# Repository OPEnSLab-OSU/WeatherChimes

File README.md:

# WeatherChimes
## Completed By: Winnie Woo, Will Richards
---
### [WeatherChimes Wiki](https://github.com/OPEnSLab-OSU/OPEnS-Lab-Home/wiki/WeatherChimes)

WeatherChimes is an Internet of Things (IoT) project that uses Loom from the OPEnS lab to send weather data from an Arduino Feather M0 to [Max](https://cycling74.com/products/max). Much like how a wind chime converts wind information into sound, WeatherChimes strives to use a variety of weather sensors to gather data and then process that information into media like generative music and visual art for users. 

## Build Guide

[WeatherChimes Build Guide PDF](https://docs.google.com/document/d/1GEz6TniiCkyVJEQ1pW2CY4VUsa4j7f_cYcETQBzS96c/edit?usp=sharing)

## Before Installation
Before code can be uploaded to the Feather, download the [Arduino IDE software](https://www.arduino.cc/en/software) and set up the board profile to include the necessary libraries such as Loom, TSL2591, SHT30 and SDI-12, instructions for completing these steps are present in our [Quick Start Guide](https://github.com/OPEnSLab-OSU/Loom-V4). 

## Before Field Deployment
Please refer to the [WeatherChimes Operation Manual](https://docs.google.com/document/d/1b8-toOKHrU17z7gMsPlmyjn5y7iMVSKRvPj8aUgFDfA/edit?usp=sharing) for best practices in understanding and deploying WeatherChimes in the field.

## Setting Up Mosquitto
Mosquitto is an MQTT broker used for handling communication with remote devices over the MQTT protocol
* Download the [Mosquitto Broker](https://mosquitto.org/download/)
* In the directory of the mosquitto folder `C:\Program Files\mosquitto>`, create a mosquitto user/password: the command below will create a user with a name of your choosing, `mosquitto_passwd -c /etc/mosquitto/pwfile *name_of_choice*`.
You will be prompted to enter a password.
* Find the mosquitto.conf file and replace it with the [mosquitto.conf](https://github.com/OPEnSLab-OSU/WeatherChimes/blob/main/MongoDB/mosquitto.conf) file in this repo. For Windows, it can be located in `C:\Program Files\mosquitto\mosquitto.conf`
* In the newly replaced mosquitto.conf now replace line 34 with the path of the pwfile you just created.
* You are now set up to run the Mosquitto exectubale file to host the MQTT broker
<br>

## Setting Up MongoDB Database
[MongoDB Manual](https://docs.mongodb.com/manual/)\
A MongoDB instance should be running on the same server as the MQTT Broker

When data is recieved by the broker it will parse the topic out into the locations that data is stored in the database.

A basic MongoDB setup should suffice in most instances, remote access may be needed which can be completed [here](https://www.digitalocean.com/community/tutorials/how-to-configure-remote-access-for-mongodb-on-ubuntu-20-04)

It is **recommended** that you utilize [MongoDB Clusters](https://www.mongodb.com/basics/clusters) (specifically replica sets) for logging data as this will allow you to utilize the Max8 framework with less work.

<br>

## Connecting MQTT to MongodB using Node-RED

* Download [Node-RED](https://nodered.org/#get-started)
* Locate the `.node-red` folder on your machine. On Windows it can be located at `C:\Users\*your_username*\.node-red`
* Replace the contents of the `.node-red` folder with all the of files in the [Node-RED](https://github.com/OPEnSLab-OSU/WeatherChimes/tree/main/MongoDB/NodeRed) folder of this repository.
* TO run Node-RED, run the command `node-red` in the terminal
* Navigate to 127.0.0.1:1880. You can do this by running "http://localhost:1880/" on a browser. This allows you to interface with the Node-RED “flows”.

### Modifying the Node-RED flow
* The flow should intially look like this:

* The node farthest to the right is the Mongodb node. Click on that node and add your MongoDB cluster that you created earlier into the *Server* field

* Next, you need to specify what broker you want to connect to. Open the MQTT node (It looks like “+/+”). Click the pencil icon next to the Server field, this will allow us to add a new MQTT server. On the following page give it a name. Specify the server address and port (Figure 18) and then under security specify the username and password you use to authenticate with the broker.

<br>

## Loom Installation and MQTT Integration

Uploading the code to the Feather WiFi requires an USB cable. 
Download the code from the WeatherChimes Github repository and put WeatherChimes.ino, arduino_secrets.h and config.h in the same folder and open in Arduino.
Go to Tools >> Board >> Loom SAMD boards V4 >> Loomified Feather M0. Then also check Tools >> Ports and see if the correct port has been selected and the board is appearing on said port. Upload the code to the Feather, after it has finished compiling, check to see if the upload was successful by opening the Arduino IDE serial monitor to see successful connections to the WiFi and MQTT broker as well as the packets of data being sent over the MQTT protocol. 

The system clock needs to be set on the first run or when the Hypnos coin cell battery is reset. 
Within the weatherchimes.ino, line 141:

`80 hypnos.setInterruptDuration(TimeSpan(0, 0, 0, 10));`

The sampling interval could be changed to any duration. From left to right, the numbers represent days, hours, minutes and seconds. 

### Getting the Arduino to connect to the internet and send to Mosquitto

The arduino_secrets.h file also needs to include the MQTT settings. The BROKER_USER and BROKER_PASSWORD correspond to the username and password set on the MQTT broker. The SECRET_BROKER is the server (IP Address / Hostname) where the MQTT Broker is listening. The BROKER_PORT is where that MQTT Broker is listening on the hostname. Finally, the SITE_NAME is not directly related to MQTT but rather the passthrough process as a whole, this tells the MongoDB server which database we should store the data in as it is passed along as the first level in the MQTT topic. 
```
2  // Wifi settings
3  #define SECRET_SSID "Example_SSID"
4  #define SECRET_PASS "Example_Pass"
5
6  // MQTT Settings
7  #define BROKER_USER "Example_User"
8  #define BROKER_PASSWORD "Example_Pass"
9  #define SECRET_BROKER "Example.broker.mosquitto.org"
10 #define BROKER_PORT 1883
11 #define SITE_NAME "WeatherChimes" //The name of the location where these  nodes will be placed
```

The instance number in the WeatherChimes.ino file also needs to be changed that can be done here, where the 1 is the instance number
```
23 Manager manager("Chime", 1);
```
<br>

## Max Patch set-up and usage
The main goal of setting up all of the MQTT connectivity and MongoDB storage of data was to create a seamless functionality to read data into [Max](https://cycling74.com/products/max). 

### Setting up the Max Patch

The MongoDB Connection Max Patch uses a Node.js script to connect to a database and receive live updated information.  
To have the Node.js script running properly ensure that Node is installed. You can do that [here]( https://nodejs.org/en/download/).  
If this is your first time using the MongoDB Max Patch and Node, click the the `Setup` button on the patch to install the necessary packages to run the main script for the patch.  

The Setup button installs the [node package manager (npm)](https://docs.npmjs.com/downloading-and-installing-node-js-and-npm) and MongoDB node package.   
The MongoDB node package can be installed using the line `npm install --mongodb`  

### Using the Max Patch
After completing the setup the user can now use the Max Patch.

To use the MongoDB Connect Max Patch, the user must input four peices of information:
1. MongoDB admin username
2. MongoDB admin password
3. [MongDB unique cluster variable](https://github.com/OPEnSLab-OSU/WeatherChimes#setting-up-mongodb-database)
4. The name of the database they would like to connect to, it should be in the Pass through script. **Example: WeatherChimes**
5. The name of the device (collection) they would like to connect to. This is declared in the config file of the weathercomplete .ino **Example: Chime1**

After all of this information is typed into the corresponding boxes, click Send, which begins the script and connects to the MongoDB database.

Data will be streamed out of the outlet of the patch, and can be used seamlessly with the Loom Sensor Max Patch to read data.

When connected successfully, if the inlet of the Max Patch receives a bang it will output the most recent data that was sent to the connected collection. This also happens upon connecting when Send is clicked.

Further additions can be made to this Patch using the MongoDB node package to get aggregated data outputs and much more. 
  - https://docs.mongodb.com/manual/
  - https://docs.mongodb.com/drivers/node/current/

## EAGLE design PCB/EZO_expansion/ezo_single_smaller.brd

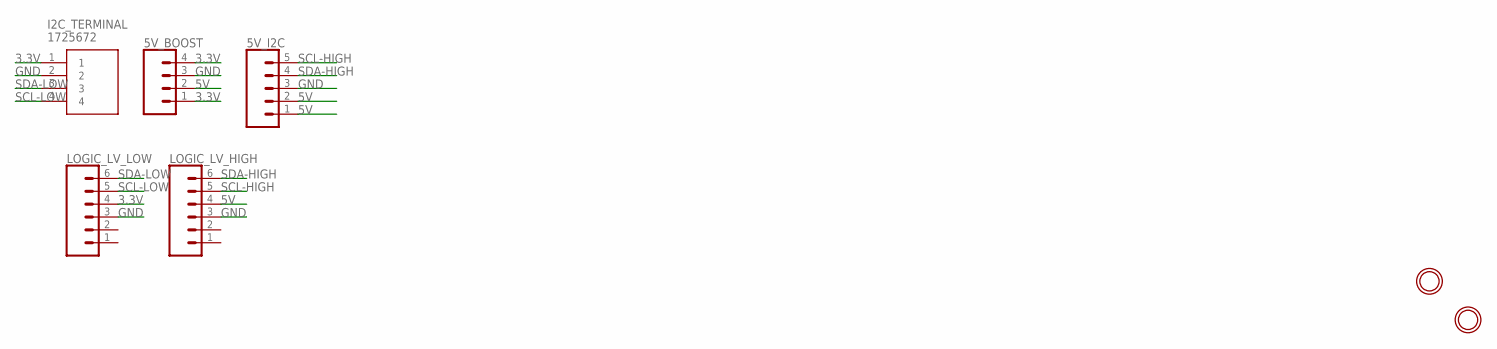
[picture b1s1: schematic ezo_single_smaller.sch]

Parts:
5V_BOOST: CONN_04PTH; 1X04
5V_I2C: CONN_05PTH; 1X05
I2C_TERMINAL: 1725672
LOGIC_LV_HIGH: CONN_06SILK_FEMALE_PTH; 1X06
LOGIC_LV_LOW: CONN_06SILK_FEMALE_PTH; 1X06
U$1, U$3: MOUNTINGHOLE2.5; MOUNTINGHOLE_2.5_PLATED

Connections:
3.3V: 5V_BOOST.1, 5V_BOOST.4, I2C_TERMINAL.1, LOGIC_LV_LOW.4
5V: 5V_BOOST.2, 5V_I2C.1, 5V_I2C.2, LOGIC_LV_HIGH.4
GND: 5V_BOOST.3, 5V_I2C.3, I2C_TERMINAL.2, LOGIC_LV_HIGH.3, LOGIC_LV_LOW.3
SCL-HIGH: 5V_I2C.5, LOGIC_LV_HIGH.5
SCL-LOW: I2C_TERMINAL.4, LOGIC_LV_LOW.5
SDA-HIGH: 5V_I2C.4, LOGIC_LV_HIGH.6
SDA-LOW: I2C_TERMINAL.3, LOGIC_LV_LOW.6

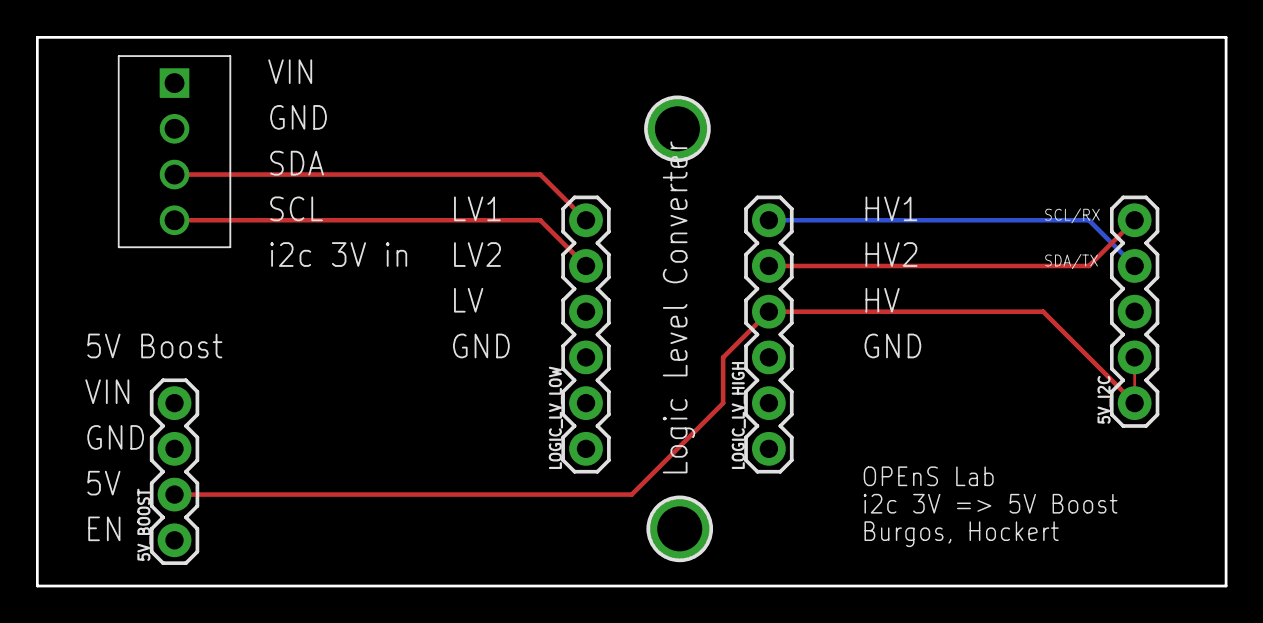
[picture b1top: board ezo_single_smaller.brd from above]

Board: 2 copper layers, 66.0 x 30.5 mm, 7 parts (0 on the bottom side), 7 nets.

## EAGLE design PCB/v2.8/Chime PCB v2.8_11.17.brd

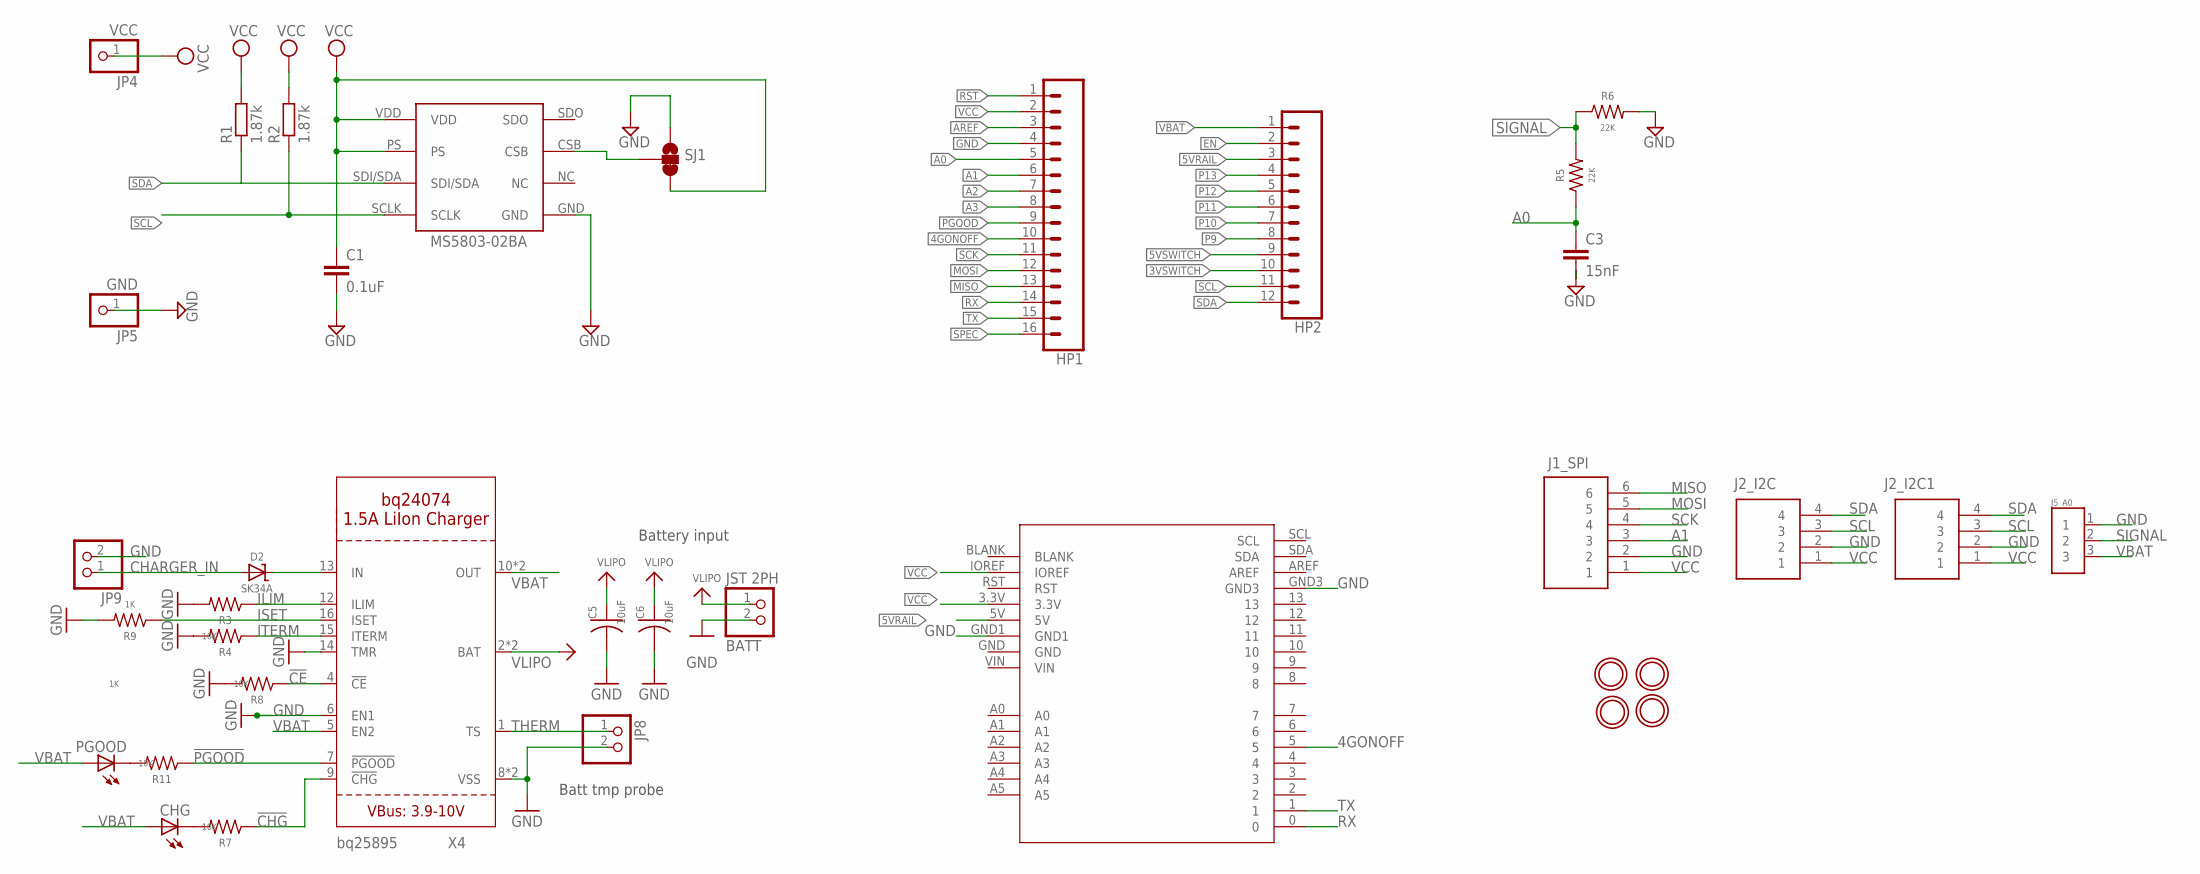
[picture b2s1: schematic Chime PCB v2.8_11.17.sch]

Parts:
BATT: JST 2PH; JST-PH-2-SMT-RA
C1: 0.1uF; C0805
C3: 15nF; C0805
C5, C6: 10uF; C0805K
CHG: LEDCHIPLED_0805; CHIPLED_0805
D2: SK34A; SMADIODE
HP1: CONN_16; 1X16
HP2: CONN_12; 1X12
J1_SPI: 1725698
J2_I2C, J2_I2C1: 1725672
J5_A0: 282834-3; TE_282834-3
JP4: VCC; 1X01
JP5: GND; 1X01
JP8, JP9: PINHD-1X2; 1X02
PGOOD: PGOOD; CHIPLED_0805
R1, R2: 1.87k; R0805
R3, R9: 1K; M0805
R4, R7, R8, R11: 10K; M0805
R5, R6: 22K; M0805
SJ1: JUMPER-SMT_3_1-NC_TRACE_SILK; SMT-JUMPER_3_1-NC_TRACE_SILK
U1: MS5803-02BA
U$1: LTE_BOARD; LTE_BOARD_FOOTPRINT
U$2, U$3, U$4, U$5: MOUNTINGHOLE2.5; MOUNTINGHOLE_2.5_PLATED
X4: BQ24074; QFN16_3MM

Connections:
3VSWITCH: HP2.10
4GONOFF: HP1.10, U$1.5
5VRAIL: HP2.3, U$1.5V
5VSWITCH: HP2.9
!CE: R8.1, X4.4 (!CE)
!CHG: R7.1, X4.9 (!CHG)
!PGOOD: R11.1, X4.7 (!PGOOD)
A0: C3.1, HP1.5, R5.1
A1: HP1.6, J1_SPI.3
A2: HP1.7
A3: HP1.8
AREF: HP1.3
CHARGER_IN: D2.A, JP9.1
EN: HP2.2
GND: BATT.2 (1), C1.2, C3.2, C5.2, C6.2, HP1.4, J1_SPI.2, J2_I2C.2, J2_I2C1.2, J5_A0.1, JP5.1, JP8.2, JP9.2, R3.2, R4.2, R6.2, R8.2, R9.2, SJ1.1, U1.GND, U$1.GND1, U$1.GND3, X4.6 (EN1), X4.8 (VSS), X4.14 (TMR), X4.THERMAL (VSS)
ILIM: R3.1, X4.12 (ILIM)
ISET: R9.1, X4.16 (ISET)
ITERM: R4.1, X4.15 (ITERM)
MISO: HP1.13, J1_SPI.6
MOSI: HP1.12, J1_SPI.5
unnamed: D2.C, X4.13 (IN)
unnamed: SJ1.2, U1.CSB
unnamed: PGOOD.C, R11.2
unnamed: CHG.C, R7.2
P9: HP2.8
P10: HP2.7
P11: HP2.6
P12: HP2.5
P13: HP2.4
PGOOD: HP1.9
RST: HP1.1
RX: HP1.14, U$1.0
SCK: HP1.11, J1_SPI.4
SCL: HP2.11, J2_I2C.3, J2_I2C1.3, R2.1, U1.SCLK
SDA: HP2.12, J2_I2C.4, J2_I2C1.4, R1.1, U1.SDI/SDA
SIGNAL: J5_A0.2, R5.2, R6.1
SPEC: HP1.16
THERM: JP8.1, X4.1 (TS)
TX: HP1.15, U$1.1
VBAT: CHG.A, HP2.1, J5_A0.3, PGOOD.A, X4.5 (EN2), X4.10 (OUT), X4.11 (OUT)
VCC: C1.1, HP1.2, J1_SPI.1, J2_I2C.1, J2_I2C1.1, JP4.1, R1.2, R2.2, SJ1.3, U1.PS, U1.VDD, U$1.3.3V, U$1.IOREF
VLIPO: BATT.1 (2), C5.1, C6.1, X4.2 (BAT), X4.3 (BAT)

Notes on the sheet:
Batt tmp probe
Battery input

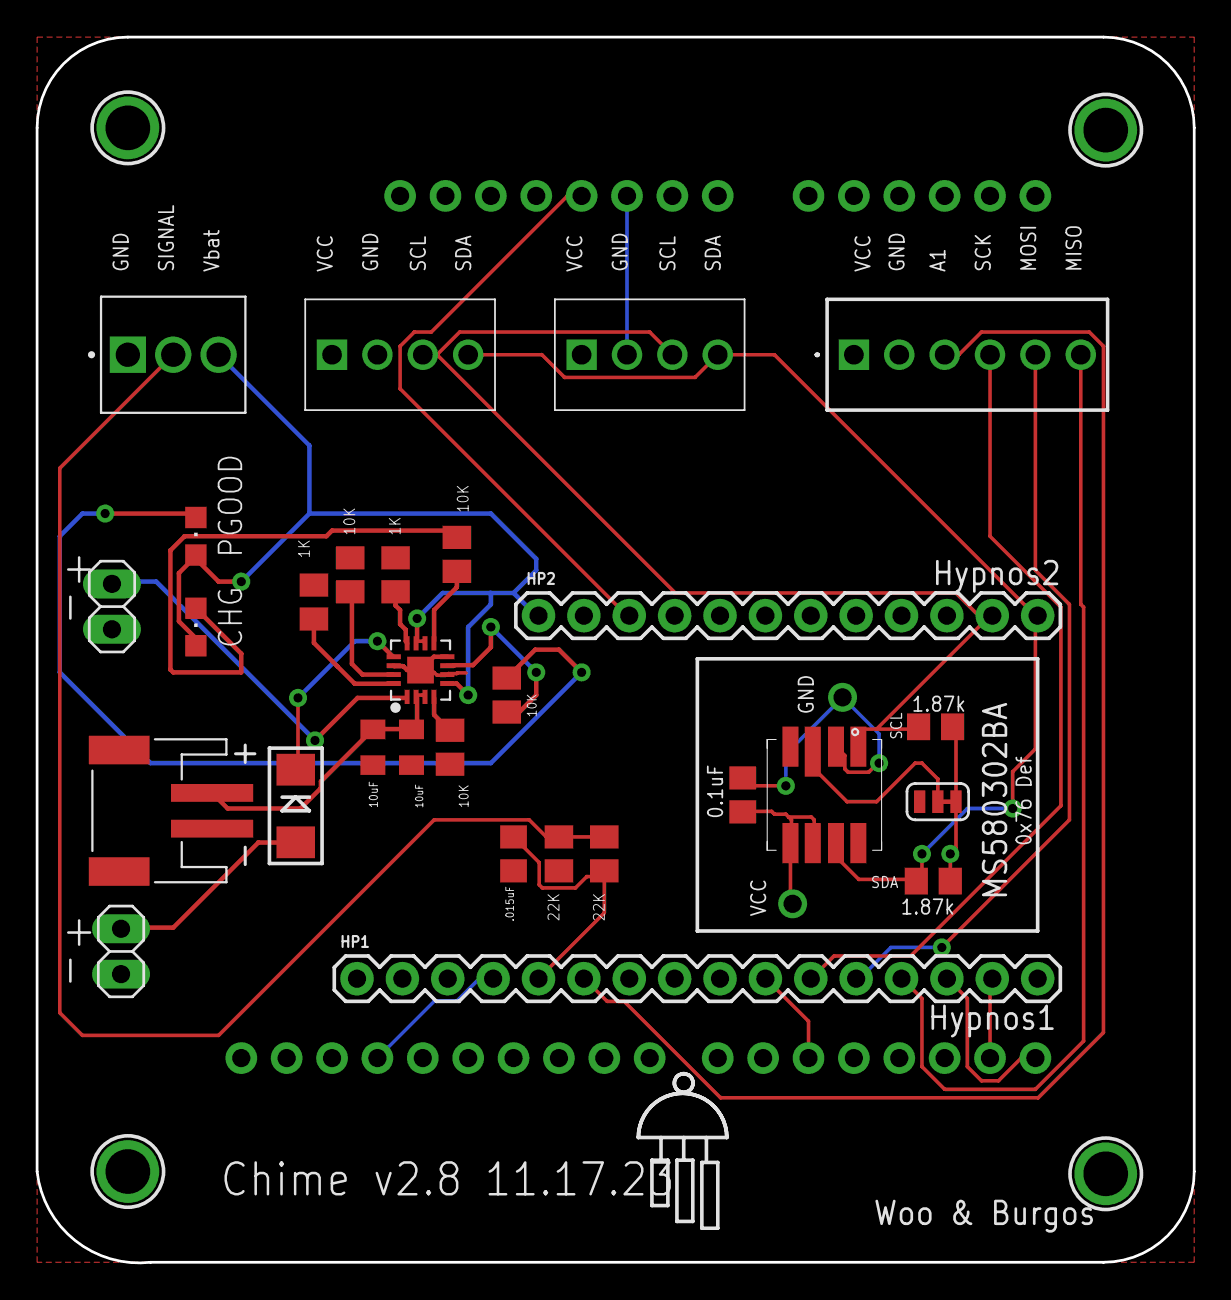
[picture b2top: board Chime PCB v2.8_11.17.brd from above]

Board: 2 copper layers, 64.8 x 68.6 mm, 36 parts (1 on the bottom side), 28 nets.

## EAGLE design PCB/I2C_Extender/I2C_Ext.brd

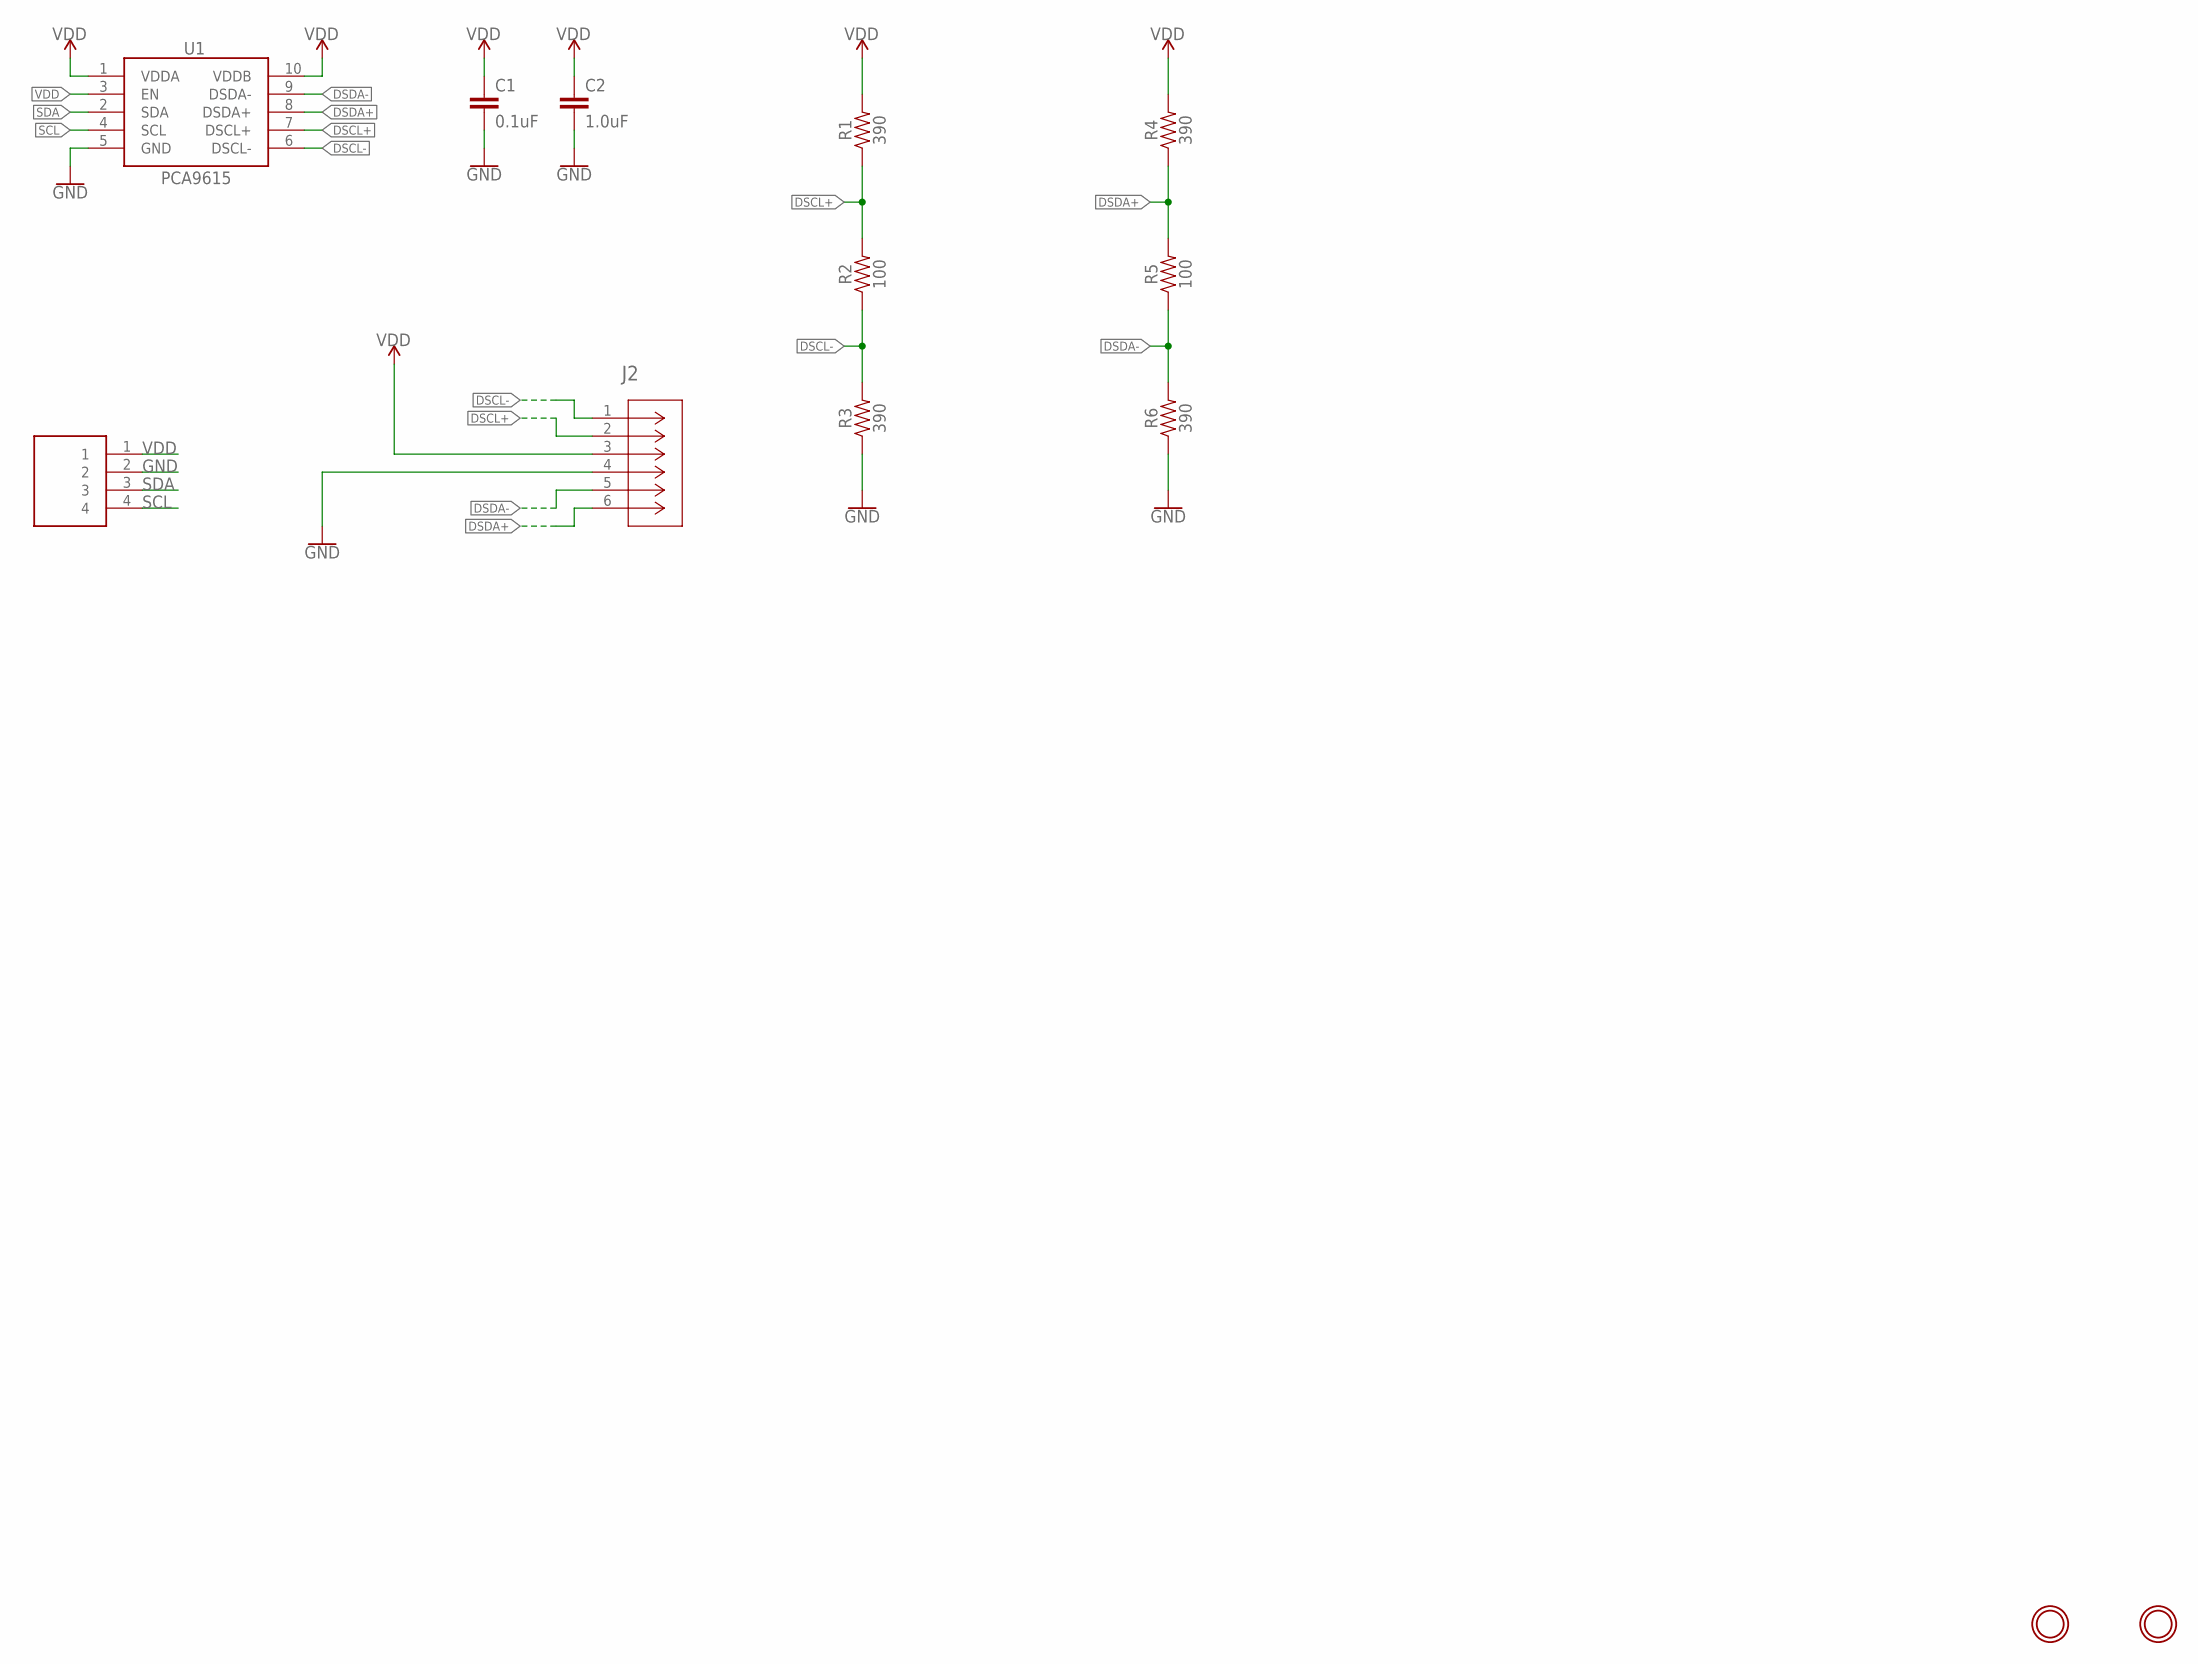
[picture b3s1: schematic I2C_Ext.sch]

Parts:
C1: 0.1uF; 0603
C2: 1.0uF; 0603
J1: 1725672
J2: 1725698; CONN_1725698_PXC
R1, R3, R4, R6: 390; 0603
R2, R5: 100; 0603
U1: PCA9615; TSSOP10
U$1, U$3: MOUNTINGHOLE2.5; MOUNTINGHOLE_2.5_PLATED

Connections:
DSCL+: J2.2, R1.1, R2.2, U1.7 (DSCL+)
DSCL-: J2.1, R2.1, R3.2, U1.6 (DSCL-)
DSDA+: J2.6, R4.1, R5.2, U1.8 (DSDA+)
DSDA-: J2.5, R5.1, R6.2, U1.9 (DSDA-)
GND: C1.2, C2.2, J1.2, J2.4, R3.1, R6.1, U1.5 (GND)
SCL: J1.4, U1.4 (SCL)
SDA: J1.3, U1.2 (SDA)
VDD: C1.1, C2.1, J1.1, J2.3, R1.2, R4.2, U1.1 (VDDA), U1.3 (EN), U1.10 (VDDB)

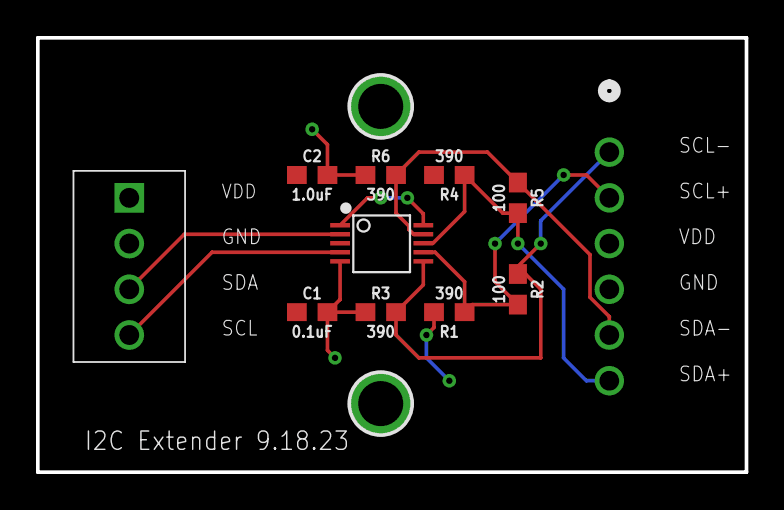
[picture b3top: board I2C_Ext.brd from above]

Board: 2 copper layers, 39.4 x 24.1 mm, 13 parts (1 on the bottom side), 8 nets.

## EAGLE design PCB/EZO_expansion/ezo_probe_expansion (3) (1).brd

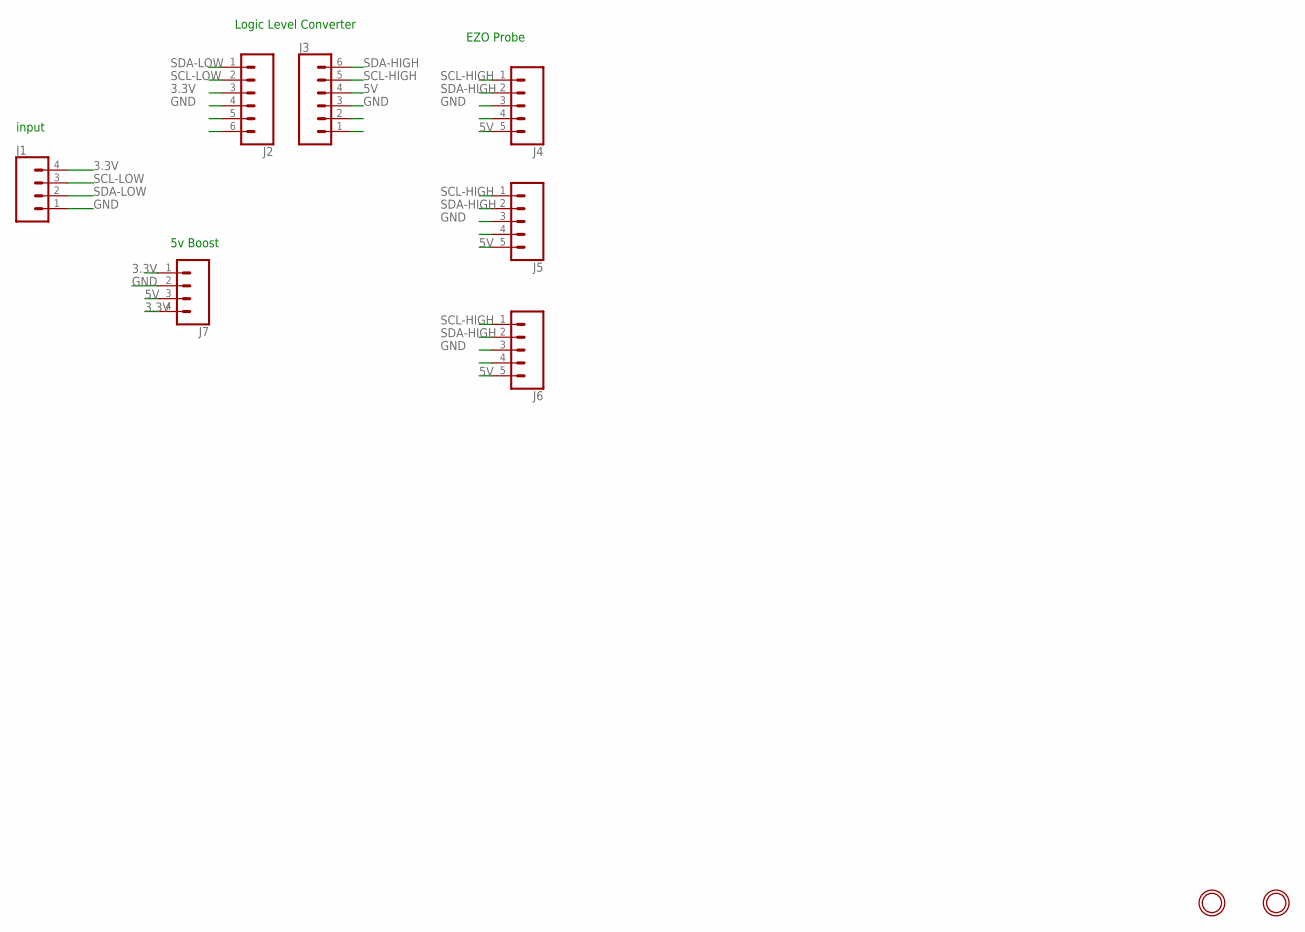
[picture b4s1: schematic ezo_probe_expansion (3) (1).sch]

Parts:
J1, J7: CONN_04PTH; 1X04
J2, J3: CONN_06SILK_FEMALE_PTH; 1X06
J4, J5, J6: CONN_05PTH; 1X05
U$1, U$2: MOUNTINGHOLE2.5; MOUNTINGHOLE_2.5_PLATED

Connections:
3.3V: J1.4, J2.3, J7.1, J7.4
5V: J3.4, J4.5, J5.5, J6.5, J7.3
GND: J1.1, J2.4, J3.3, J4.3, J5.3, J6.3, J7.2
SCL-HIGH: J3.5, J4.1, J5.1, J6.1
SCL-LOW: J1.3, J2.2
SDA-HIGH: J3.6, J4.2, J5.2, J6.2
SDA-LOW: J1.2, J2.1

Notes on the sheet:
input
Logic Level Converter
EZO Probe
5v Boost

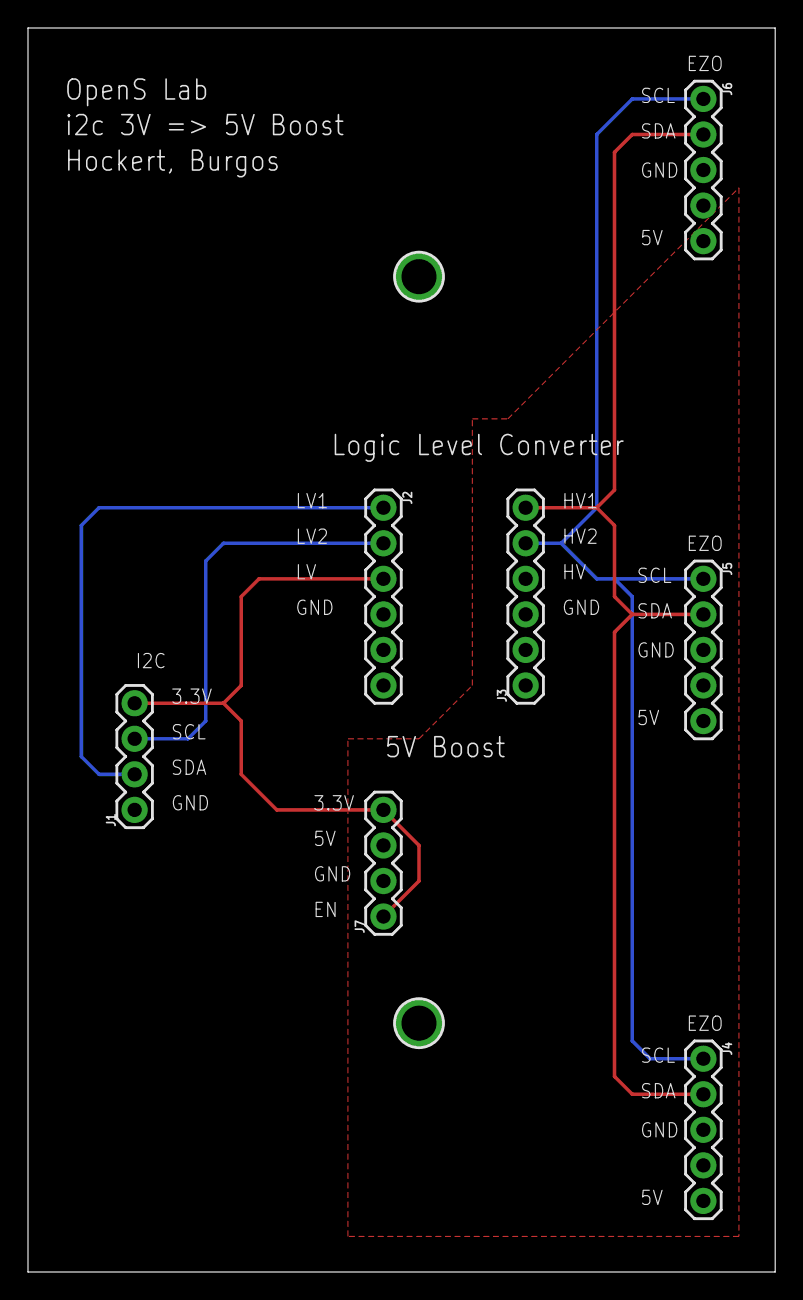
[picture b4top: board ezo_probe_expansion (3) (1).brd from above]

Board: 2 copper layers, 53.4 x 88.9 mm, 9 parts (0 on the bottom side), 7 nets.

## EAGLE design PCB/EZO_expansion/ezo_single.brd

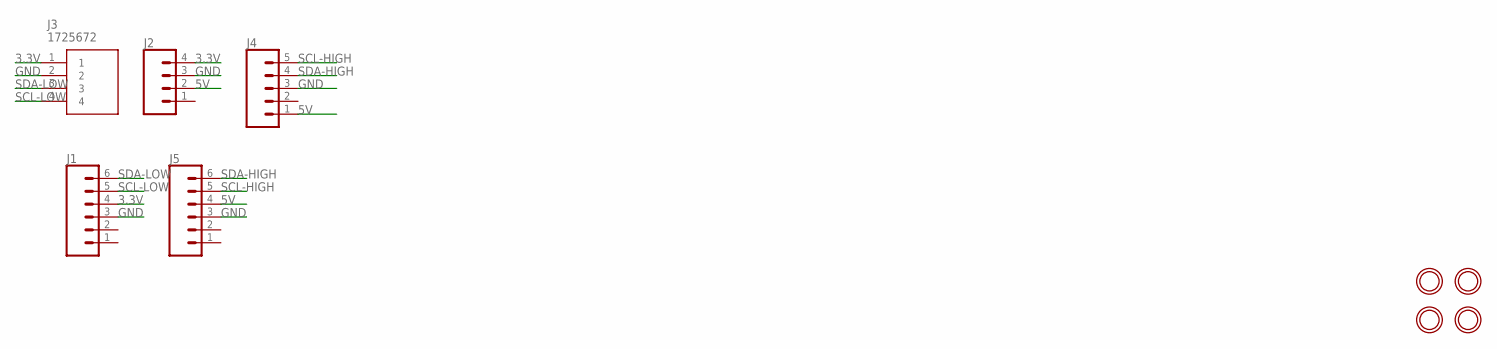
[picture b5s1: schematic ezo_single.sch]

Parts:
J1, J5: CONN_06SILK_FEMALE_PTH; 1X06
J2: CONN_04PTH; 1X04
J3: 1725672
J4: CONN_05PTH; 1X05
U$1, U$2, U$3, U$4: MOUNTINGHOLE2.5; MOUNTINGHOLE_2.5_PLATED

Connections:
3.3V: J1.4, J2.4, J3.1
5V: J2.2, J4.1, J5.4
GND: J1.3, J2.3, J3.2, J4.3, J5.3
SCL-HIGH: J4.5, J5.5
SCL-LOW: J1.5, J3.4
SDA-HIGH: J4.4, J5.6
SDA-LOW: J1.6, J3.3

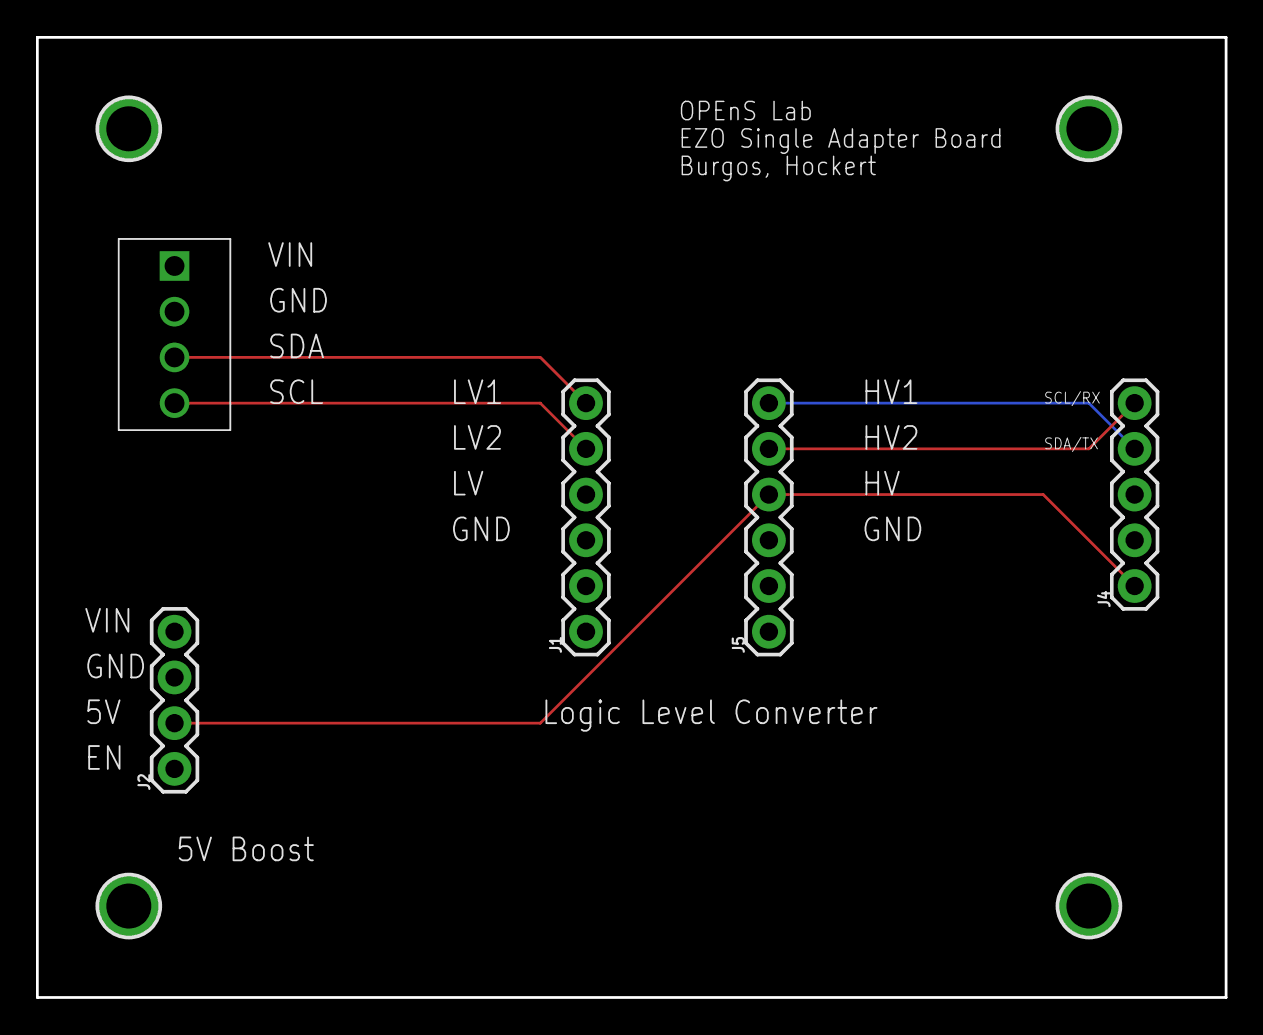
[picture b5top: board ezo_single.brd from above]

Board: 2 copper layers, 66.0 x 53.3 mm, 9 parts (0 on the bottom side), 7 nets.

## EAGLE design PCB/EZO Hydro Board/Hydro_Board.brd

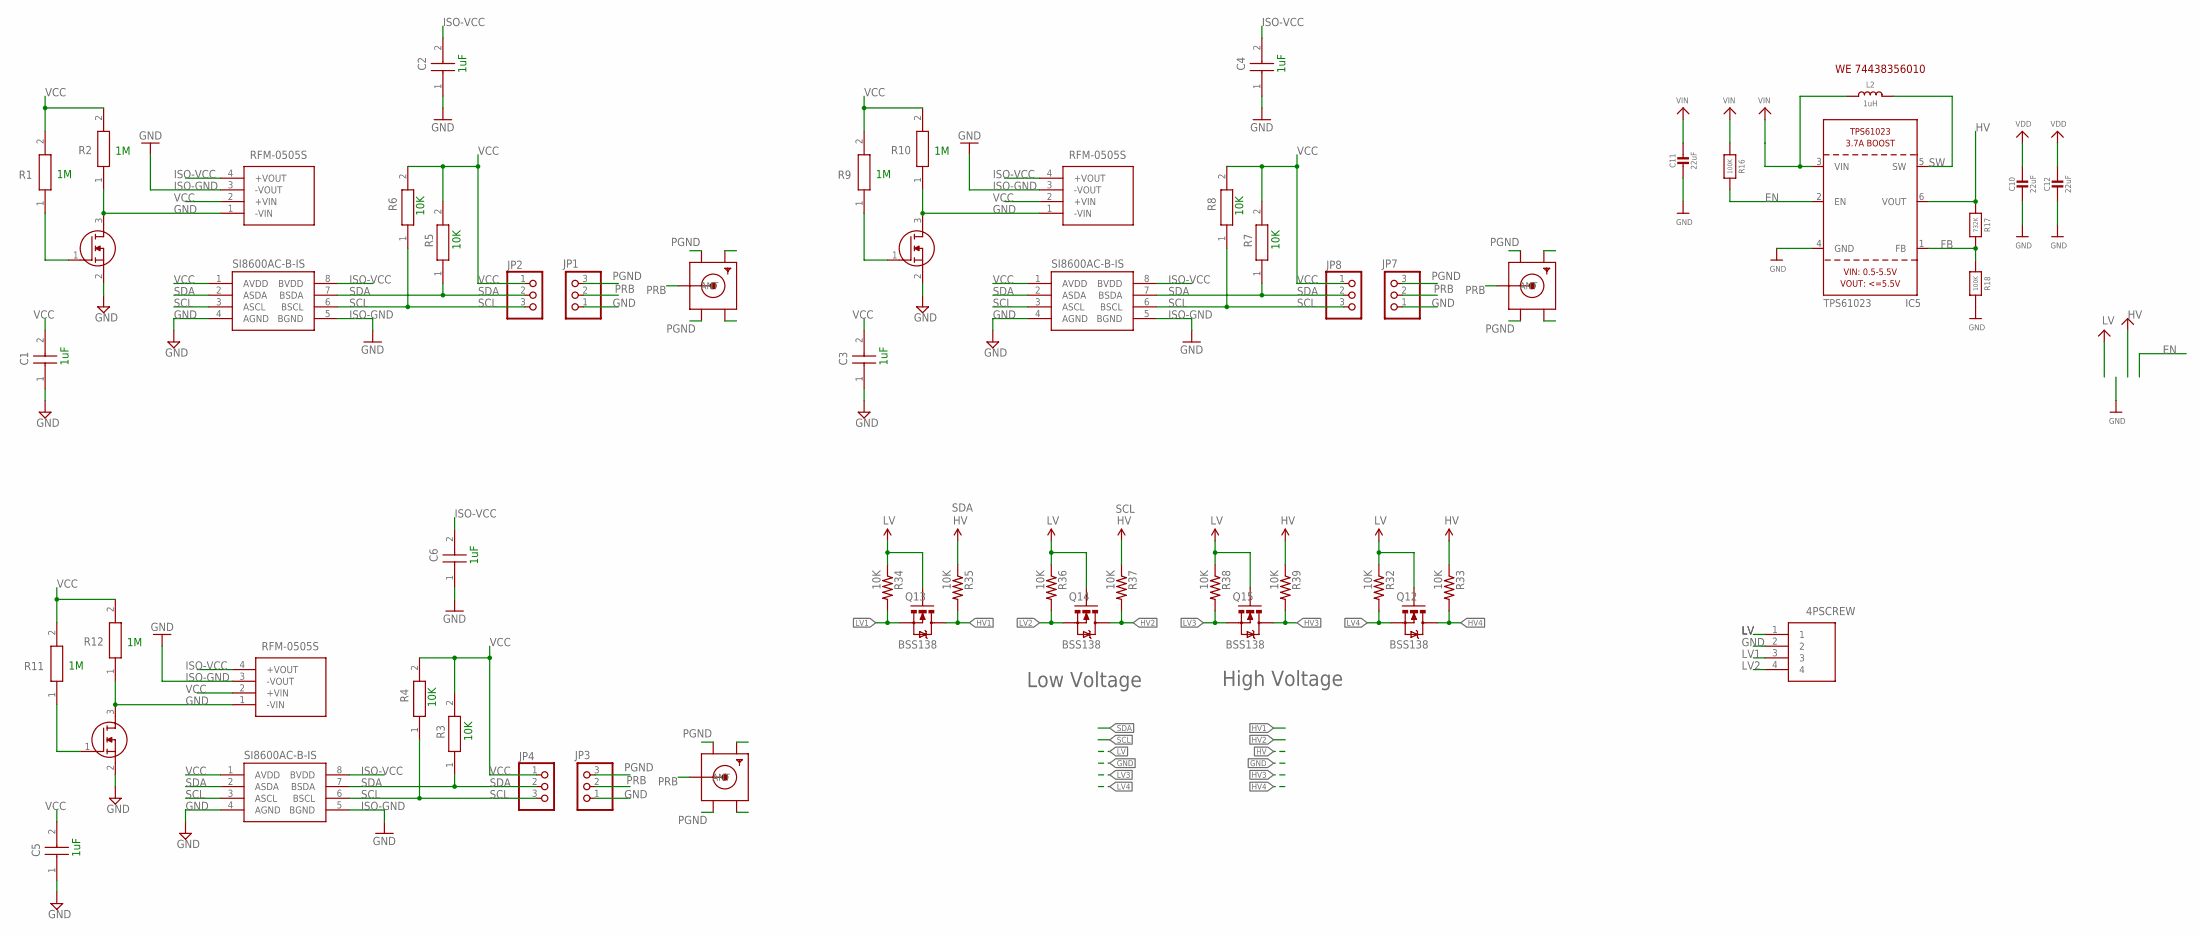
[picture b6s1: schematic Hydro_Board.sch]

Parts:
4PSCREW: 1725672
C1, C2, C3, C4, C5, C6: C1608X5R1E105K080AC; CAPC1608X80N
C10, C11, C12: 22uF; 0805-NO
IC1, IC2, IC4: SI8600AC-B-IS; SOIC127P600X175-8N
IC5: TPS61023; SOT563
JP1, JP2, JP3, JP4, JP7, JP8: PINHD-1X3; 1X03
L2: 1uH; INDUCTOR_5X5MM_TDK_VLC5045
PS1, PS3, PS4: RFM-0505S; RFM0505S
Q1, Q2, Q3: BSS119NH6327XTSA1; SOT95P260X110-3N
Q12, Q13, Q14, Q15: BSS138; SOT23-3
R1, R2, R9, R10, R11, R12: ERJ-3EKF1004V; RESC1608X55N
R3, R4, R5, R6, R7, R8: CRCW060310K0FKEAHP; RESC1608X50N
R16, R18: 100K; 0603-NO
R17: 732K; 0603-NO
R32, R33, R34, R35, R36, R37, R38, R39: 10K; 0603-RES
X1, X2, X4: SMACONNECTOR_EDGE; SMA_EDGELAUNCH

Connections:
EN: IC5.2 (EN), R16.2
FB: IC5.1 (FB), R17.2, R18.1
GND: 4PSCREW.2, C1.1, C2.1, C3.1, C5.1, C10.2, C11.2, C12.2, IC1.4 (AGND), IC2.4 (AGND), IC4.4 (AGND), IC5.4 (GND), JP1.1, JP3.1, JP7.1, PS1.1 (-VIN), PS3.1 (-VIN), PS4.1 (-VIN), Q1.2 (S), Q1.3 (D), Q2.2 (S), Q2.3 (D), Q3.2 (S), Q3.3 (D), R2.1, R10.1, R12.1, R18.2
HV: IC5.6 (VOUT), R17.1, R33.1, R39.1
HV1: Q13.3 (D), R35.2
HV2: Q14.3 (D), R37.2
HV3: Q15.3 (D), R39.2
HV4: Q12.3 (D), R33.2
ISO-GND: IC1.5 (BGND), IC2.5 (BGND), IC4.5 (BGND), PS1.3 (-VOUT), PS3.3 (-VOUT), PS4.3 (-VOUT)
ISO-VCC: C2.2, C4.2, C6.2, IC1.8 (BVDD), IC2.8 (BVDD), IC4.8 (BVDD), PS1.4 (+VOUT), PS3.4 (+VOUT), PS4.4 (+VOUT)
LV: 4PSCREW.1, IC5.3 (VIN), L2.P$1 (1), Q12.1 (G), Q13.1 (G), Q14.1 (G), Q15.1 (G), R32.1, R34.1, R36.1, R38.1
LV1: 4PSCREW.3, Q13.2 (S), R34.2
LV2: 4PSCREW.4, Q14.2 (S), R36.2
LV3: Q15.2 (S), R38.2
LV4: Q12.2 (S), R32.2
unnamed: Q1.1 (G), R1.1
unnamed: Q3.1 (G), R11.1
unnamed: Q2.1 (G), R9.1
PGND: JP1.3, JP3.3, JP7.3, X1.GND@2 (GND3), X1.GND@4 (GND1), X2.GND@2 (GND3), X2.GND@4 (GND1), X4.GND@2 (GND3), X4.GND@4 (GND1)
PRB: JP1.2, JP3.2, JP7.2, X1.P (ANT), X2.P (ANT), X4.P (ANT)
SCL: IC1.3 (ASCL), IC1.6 (BSCL), IC2.3 (ASCL), IC2.6 (BSCL), IC4.3 (ASCL), IC4.6 (BSCL), JP2.3, JP4.3, JP8.3, R4.1, R6.1, R8.1, R37.1
SDA: IC1.2 (ASDA), IC1.7 (BSDA), IC2.2 (ASDA), IC2.7 (BSDA), IC4.2 (ASDA), IC4.7 (BSDA), JP2.2, JP4.2, JP8.2, R3.1, R5.1, R7.1, R35.1
SW: IC5.5 (SW), L2.P$2 (2)
VCC: C1.2, C3.2, C5.2, IC1.1 (AVDD), IC2.1 (AVDD), IC4.1 (AVDD), JP2.1, JP4.1, JP8.1, PS1.2 (+VIN), PS3.2 (+VIN), PS4.2 (+VIN), R1.2, R2.2, R3.2, R4.2, R5.2, R6.2, R7.2, R8.2, R9.2, R10.2, R11.2, R12.2
VDD: C10.1, C12.1
VIN: C11.1, R16.1

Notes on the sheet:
10K
1uF
High Voltage
Low Voltage
WE 74438356010

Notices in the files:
parts and their libraries:
microbuilder: This work is placed in the public domain, and may be freely used for commercial and non-commercial work with the following conditions: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
SparkFun-Connectors: Licensing: Creative Commons ShareAlike 4.0 International - https://creativecommons.org/licenses/by-sa/4.0
